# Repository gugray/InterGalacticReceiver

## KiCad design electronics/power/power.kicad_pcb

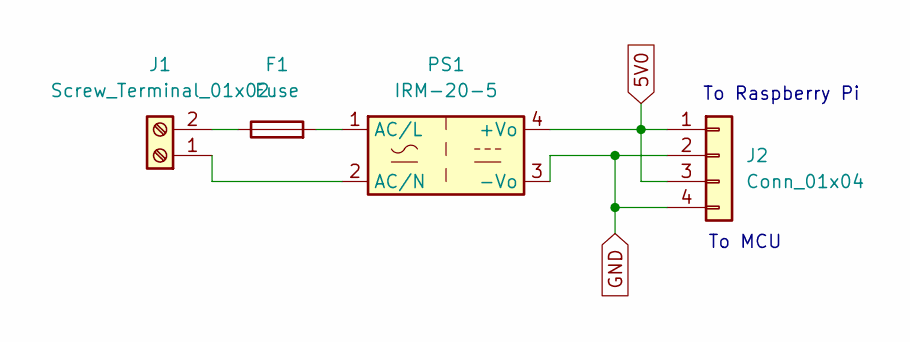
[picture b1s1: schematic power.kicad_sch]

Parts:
F1: Fuse; FuseSocket
J1: Screw_Terminal_01x02; TerminalBlock_4Ucon_1x02_P3.50mm_Horizontal
J2: Conn_01x04; PinHeader_1x04_P2.54mm_Vertical
PS1: IRM-20-5; Converter_ACDC_MeanWell_IRM-20-xx_THT

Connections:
5V0: J2.1, J2.3, PS1.4 (+Vo)
GND: J2.2, J2.4, PS1.3 (-Vo)
unnamed: J1.1, PS1.2 (AC/N)
unnamed: F1.1, J1.2
unnamed: F1.2, PS1.1 (AC/L)

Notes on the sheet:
To MCU
To Raspberry Pi

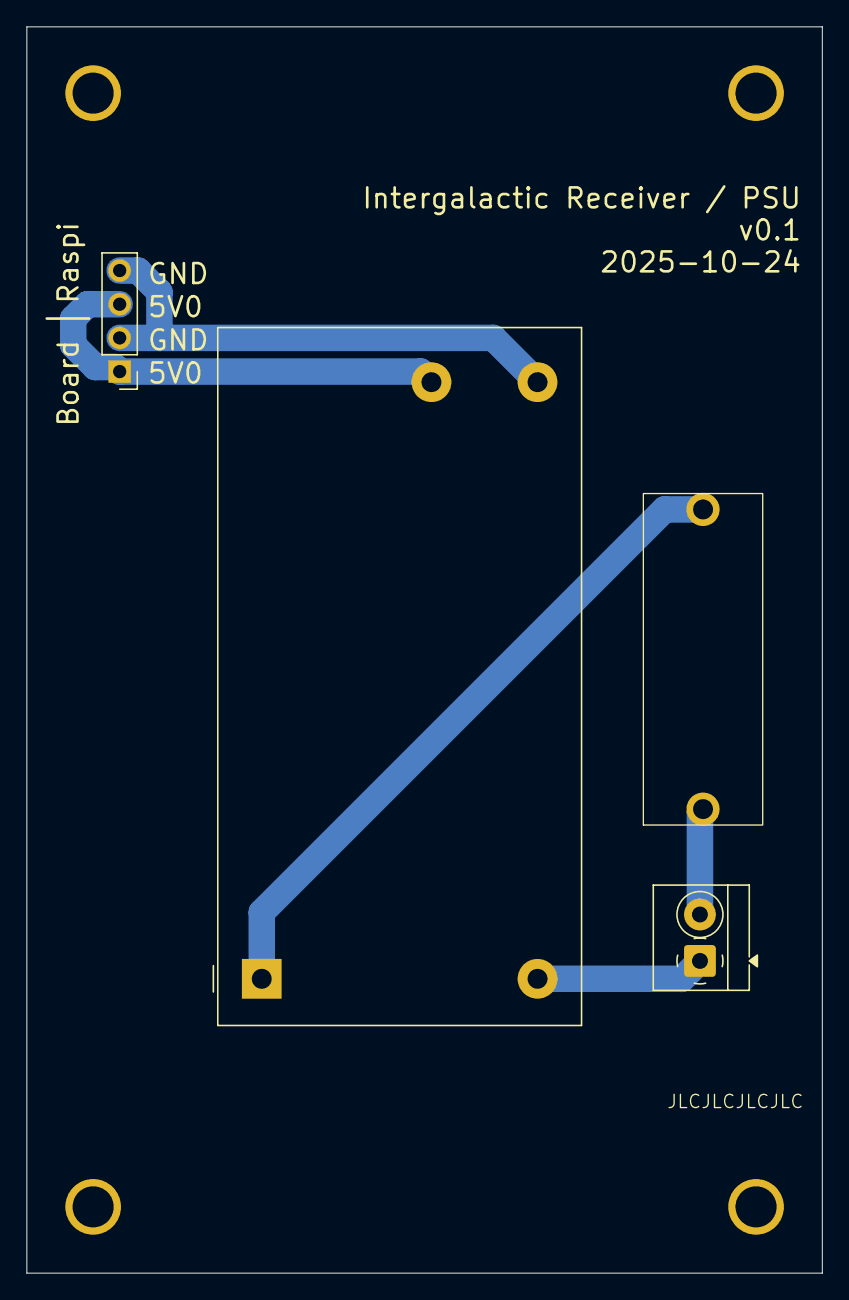
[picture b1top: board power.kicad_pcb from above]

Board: 2 copper layers, 60.0 x 94.0 mm, 4 parts (0 on the bottom side), 5 nets.

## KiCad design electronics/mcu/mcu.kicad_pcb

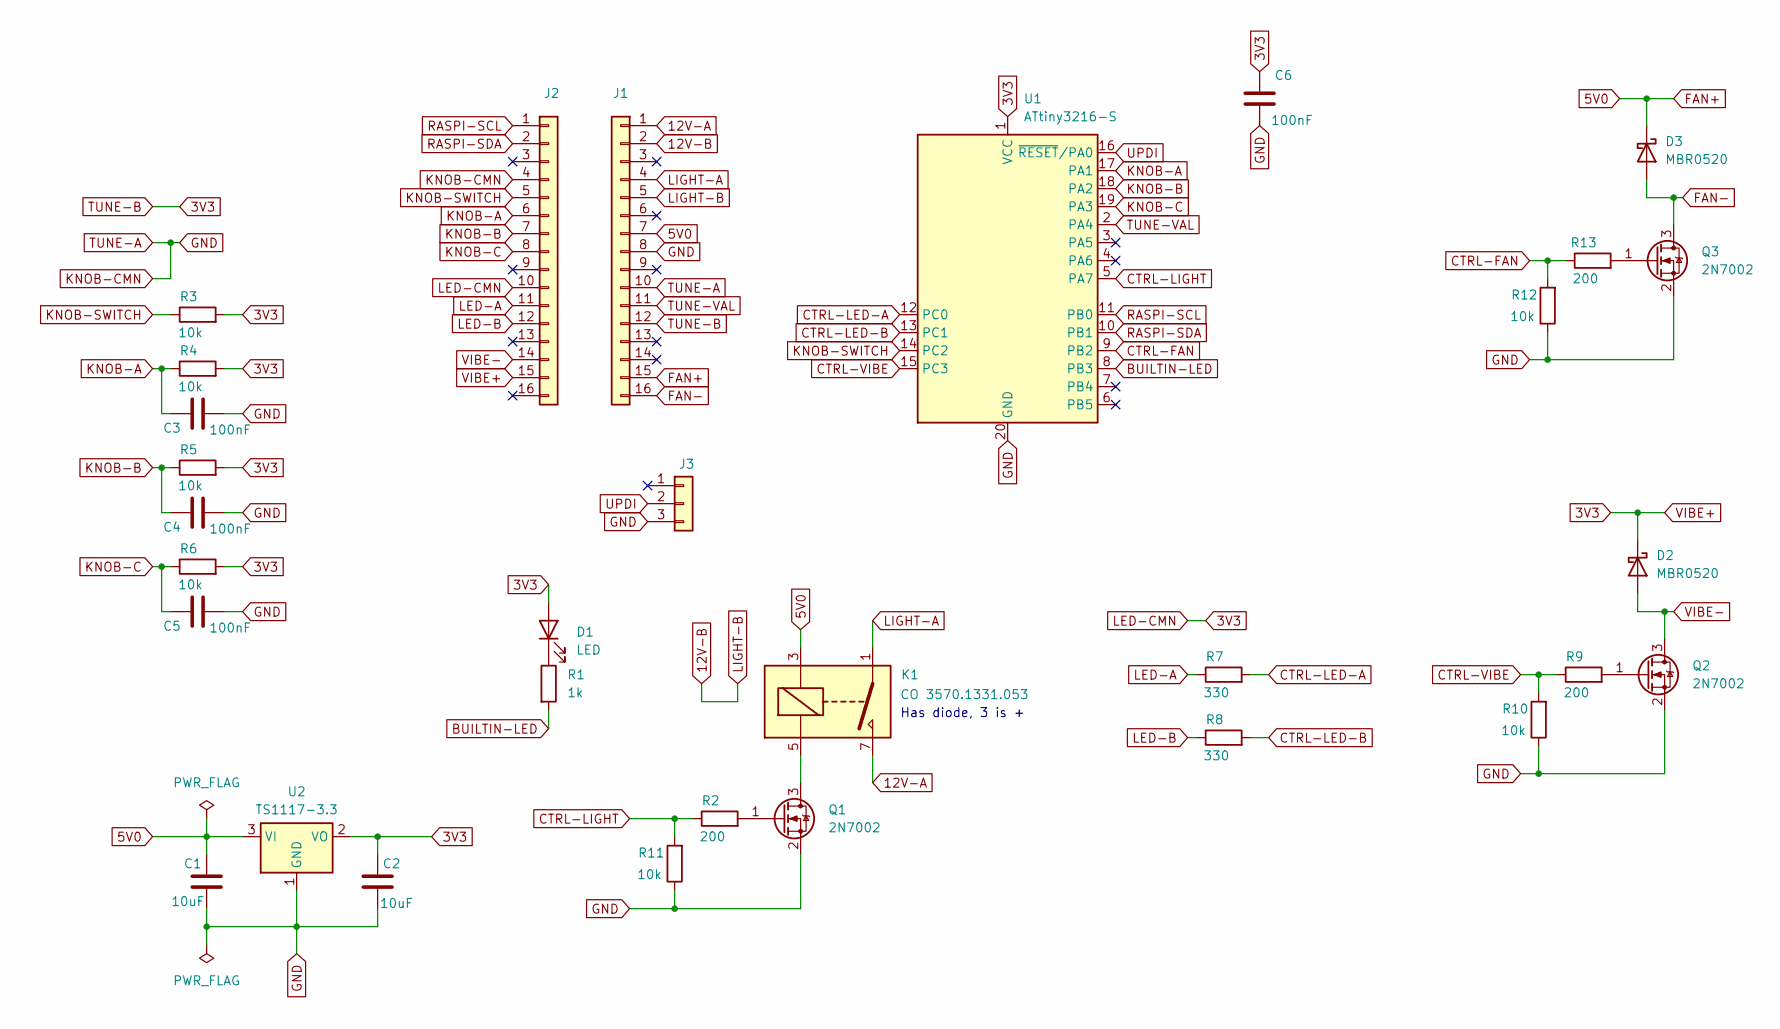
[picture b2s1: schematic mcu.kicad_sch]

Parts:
C1, C2: 10uF; C_0805_2012Metric
C3, C4, C5, C6: 100nF; C_0805_2012Metric
D1: LED; LED_0805_2012Metric
D2, D3: MBR0520; D_SOD-123
J1, J2: Conn_01x16; PinSocket_1x16_P2.54mm_Vertical
J3: Conn_01x03; PinHeader_1x03_P2.54mm_Vertical
K1: CO 3570.1331.053; Relay_SPST_StandexMeder_SIL_Form1A
Q1, Q2, Q3: 2N7002; SOT-23
R1: 1k; C_0805_2012Metric
R2, R9, R13: 200; C_0805_2012Metric
R3, R4, R5, R6, R10, R11, R12: 10k; C_0805_2012Metric
R7, R8: 330; C_0805_2012Metric
U1: ATtiny3216-S; SOIC-20W_7.5x12.8mm_P1.27mm
U2: TS1117-3.3; SOT-223-3_TabPin2

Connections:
3V3: C2.1, C6.1, D1.2 (A), D2.1 (K), J1.12, J2.10, J2.15, R3.2, R4.2, R5.2, R6.2, U1.1 (VCC), U2.2 (VO)
5V0: C1.1, D3.1 (K), J1.7, J1.15, K1.3, U2.3 (VI)
12V-A: J1.1, K1.7
12V-B: J1.2, J1.5
BUILTIN-LED: R1.2, U1.8 (PB3)
CTRL-FAN: R12.2, R13.1, U1.9 (PB2)
CTRL-LED-A: R7.2, U1.12 (PC0)
CTRL-LED-B: R8.2, U1.13 (PC1)
CTRL-LIGHT: R2.1, R11.2, U1.5 (PA7)
CTRL-VIBE: R9.1, R10.2, U1.15 (PC3)
FAN-: D3.2 (A), J1.16, Q3.3 (D)
GND: C1.2, C2.2, C3.2, C4.2, C5.2, C6.2, J1.8, J1.10, J2.4, J3.3, Q1.2 (S), Q2.2 (S), Q3.2 (S), R10.1, R11.1, R12.1, U1.20 (GND), U2.1 (GND)
KNOB-A: C3.1, J2.6, R4.1, U1.17 (PA1)
KNOB-B: C4.1, J2.7, R5.1, U1.18 (PA2)
KNOB-C: C5.1, J2.8, R6.1, U1.19 (PA3)
KNOB-SWITCH: J2.5, R3.1, U1.14 (PC2)
LED-A: J2.11, R7.1
LED-B: J2.12, R8.1
LIGHT-A: J1.4, K1.1
unnamed: D1.1 (K), R1.1
unnamed: K1.5, Q1.3 (D)
unnamed: Q1.1 (G), R2.2
unnamed: Q2.1 (G), R9.2
unnamed: Q3.1 (G), R13.2
RASPI-SCL: J2.1, U1.11 (PB0)
RASPI-SDA: J2.2, U1.10 (PB1)
TUNE-VAL: J1.11, U1.2 (PA4)
UPDI: J3.2, U1.16 (~RESET/PA0)
VIBE-: D2.2 (A), J2.14, Q2.3 (D)

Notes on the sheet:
Has diode, 3 is +

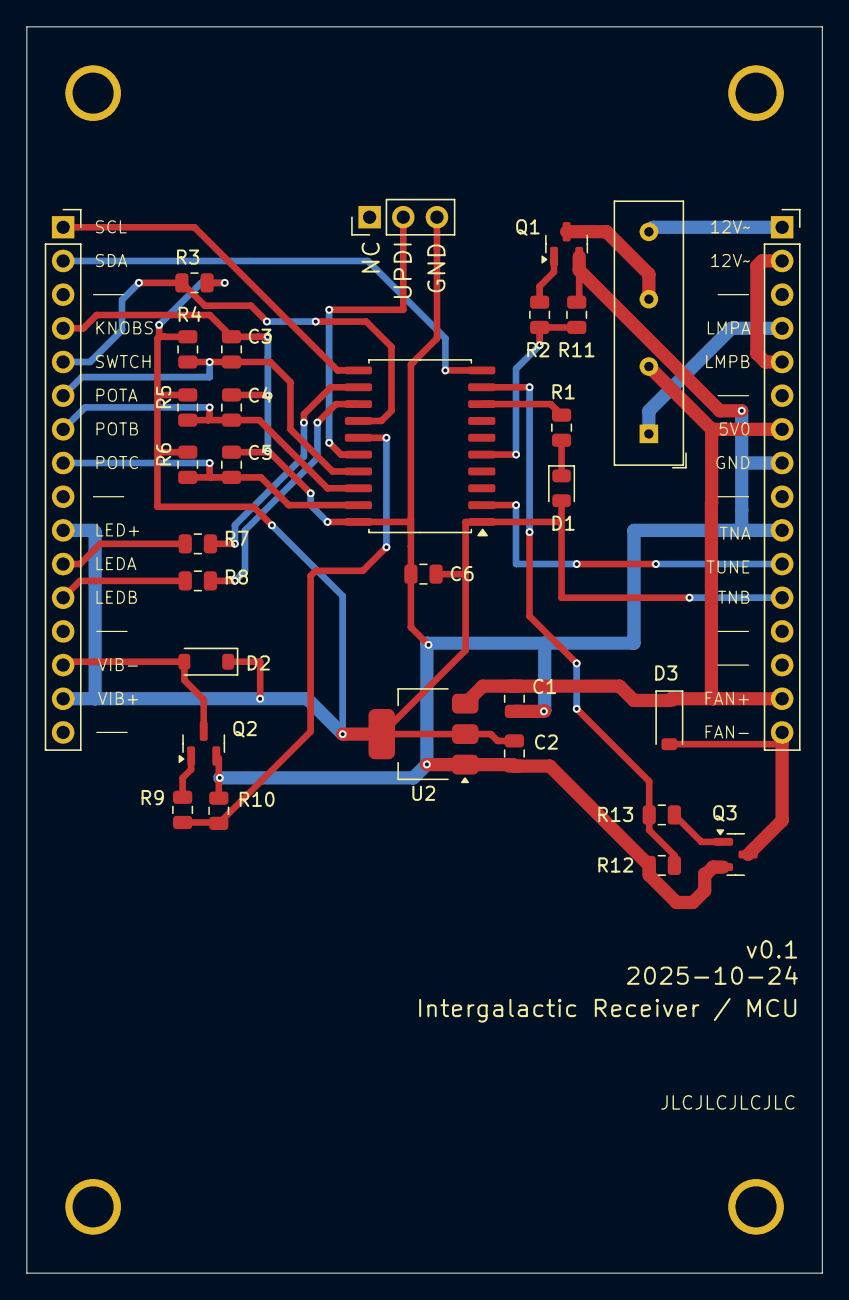
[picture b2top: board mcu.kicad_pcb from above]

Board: 2 copper layers, 60.0 x 94.0 mm, 31 parts (0 on the bottom side), 29 nets.

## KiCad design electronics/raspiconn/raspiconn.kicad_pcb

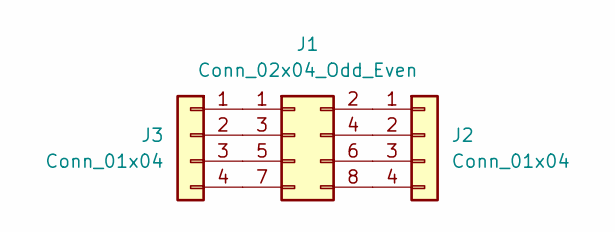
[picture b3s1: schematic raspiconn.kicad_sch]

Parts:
J1: Conn_02x04_Odd_Even; PinSocket_2x04_P2.54mm_Vertical
J2, J3: Conn_01x04; PinHeader_1x04_P2.54mm_Vertical

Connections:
unnamed: J1.1, J3.1
unnamed: J1.2, J2.1
unnamed: J1.3, J3.2
unnamed: J1.4, J2.2
unnamed: J1.5, J3.3
unnamed: J1.6, J2.3
unnamed: J1.7, J3.4
unnamed: J1.8, J2.4

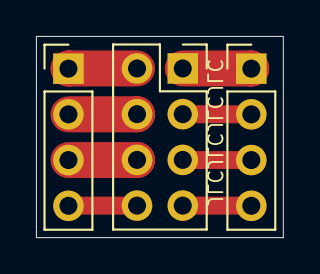
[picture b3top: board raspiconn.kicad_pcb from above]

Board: 2 copper layers, 13.7 x 11.2 mm, 3 parts (0 on the bottom side), 8 nets.

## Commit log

2025-10-29 initial commit / wip
2025-11-03 i2c wip
2025-11-07 teaser page
2025-11-07 teaser page: hydra
2025-11-21 i2c hardware controller in dedicated file with bg thread
2026-03-02 update raspi setup docs
2026-03-02 Revert "make work on linux"
    This reverts commit de673e6c017a8106eed1d8b97fcb2d1416e7523c.
    # Conflicts:
    # code-raspi/src/horrors.cpp
2026-03-02 re-add generated shaders.h
2026-03-02 checksum on MCU data
2026-03-02 LED behavior tweaks in MCU
2026-03-02 update notes
2026-03-02 backlight not controlled by main switch; off command
2026-03-02 fix static with random uniform
2026-03-02 turn off lights when exiting
2026-03-02 not rendering station behind static
2026-03-02 info overlay wip
2026-03-03 info overlay
2026-03-03 aBe sketch update
2026-03-03 morisil broadcast
2026-03-04 update shader names/titles
2026-03-04 remove datasheets
